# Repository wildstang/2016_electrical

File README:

This is the 2015 electrical repository.

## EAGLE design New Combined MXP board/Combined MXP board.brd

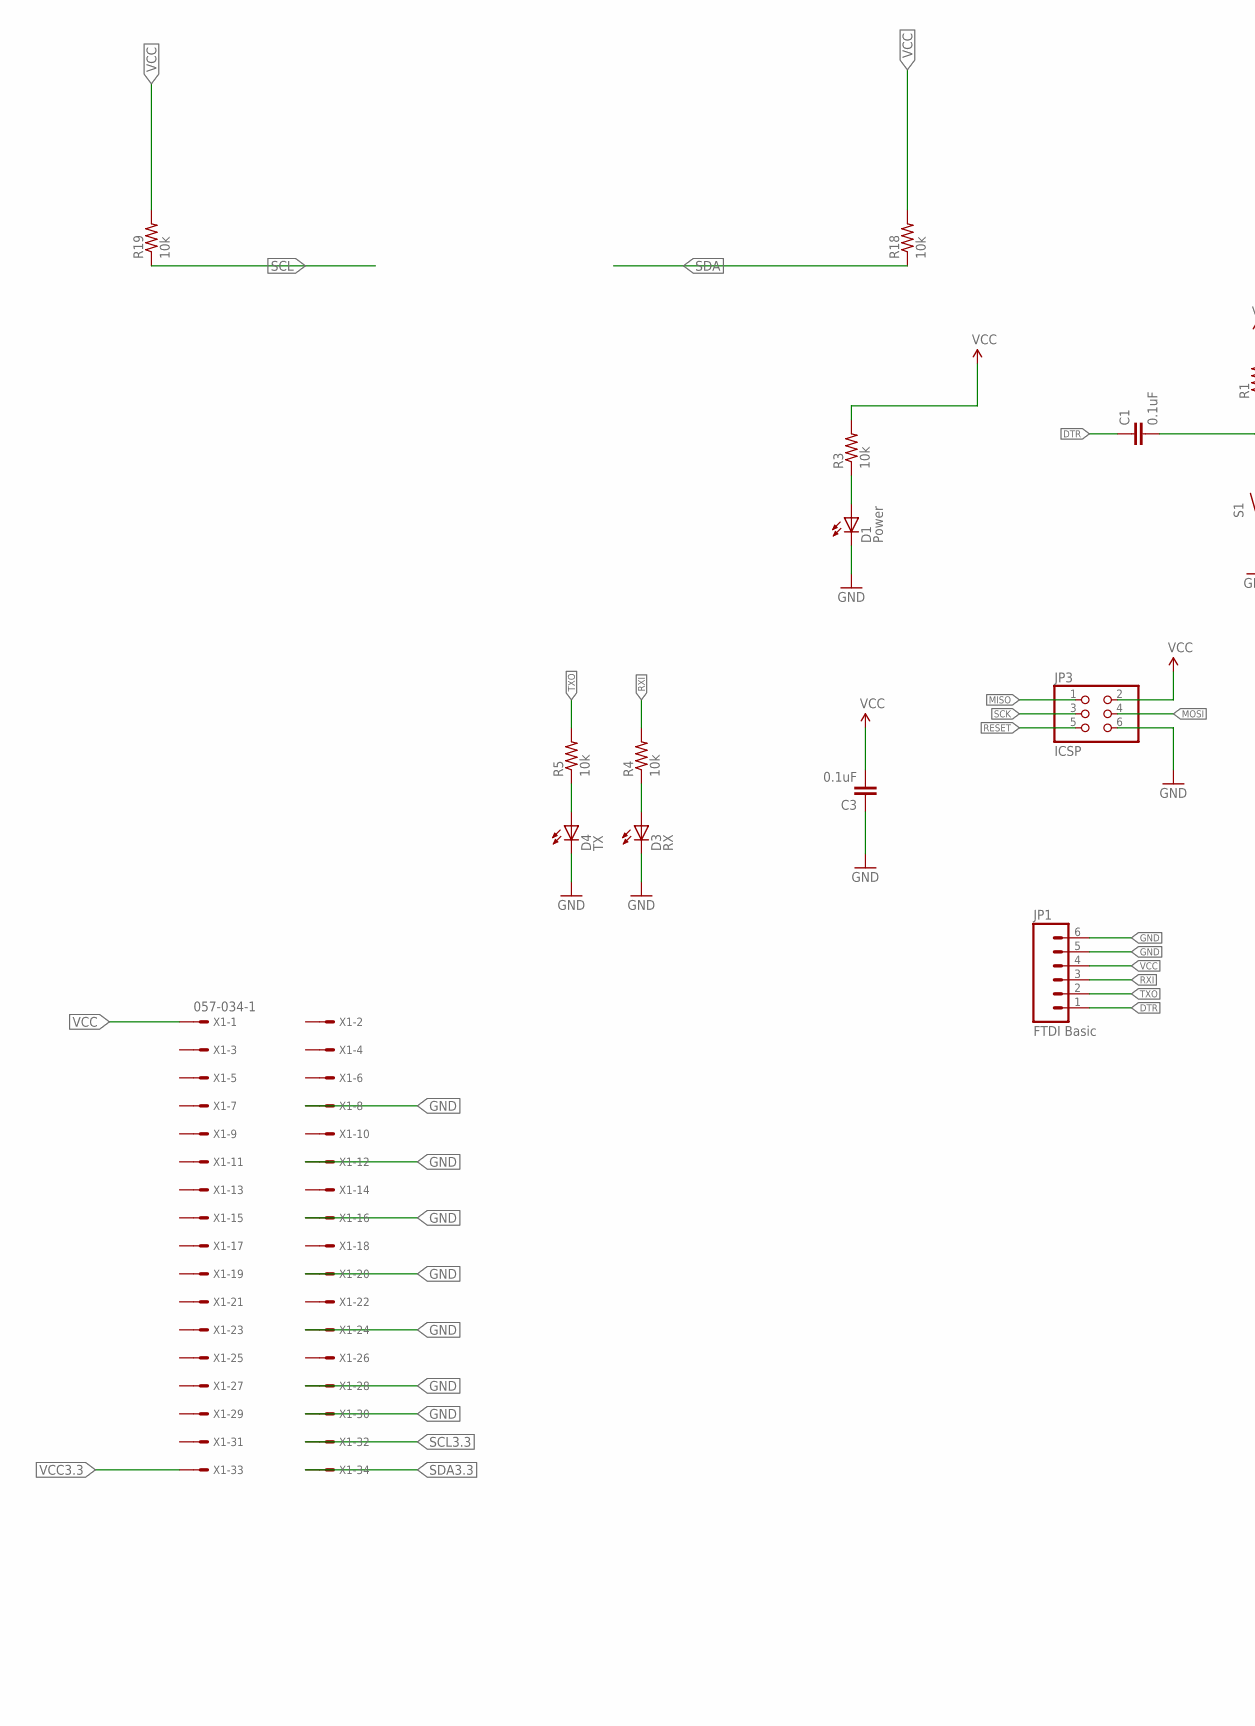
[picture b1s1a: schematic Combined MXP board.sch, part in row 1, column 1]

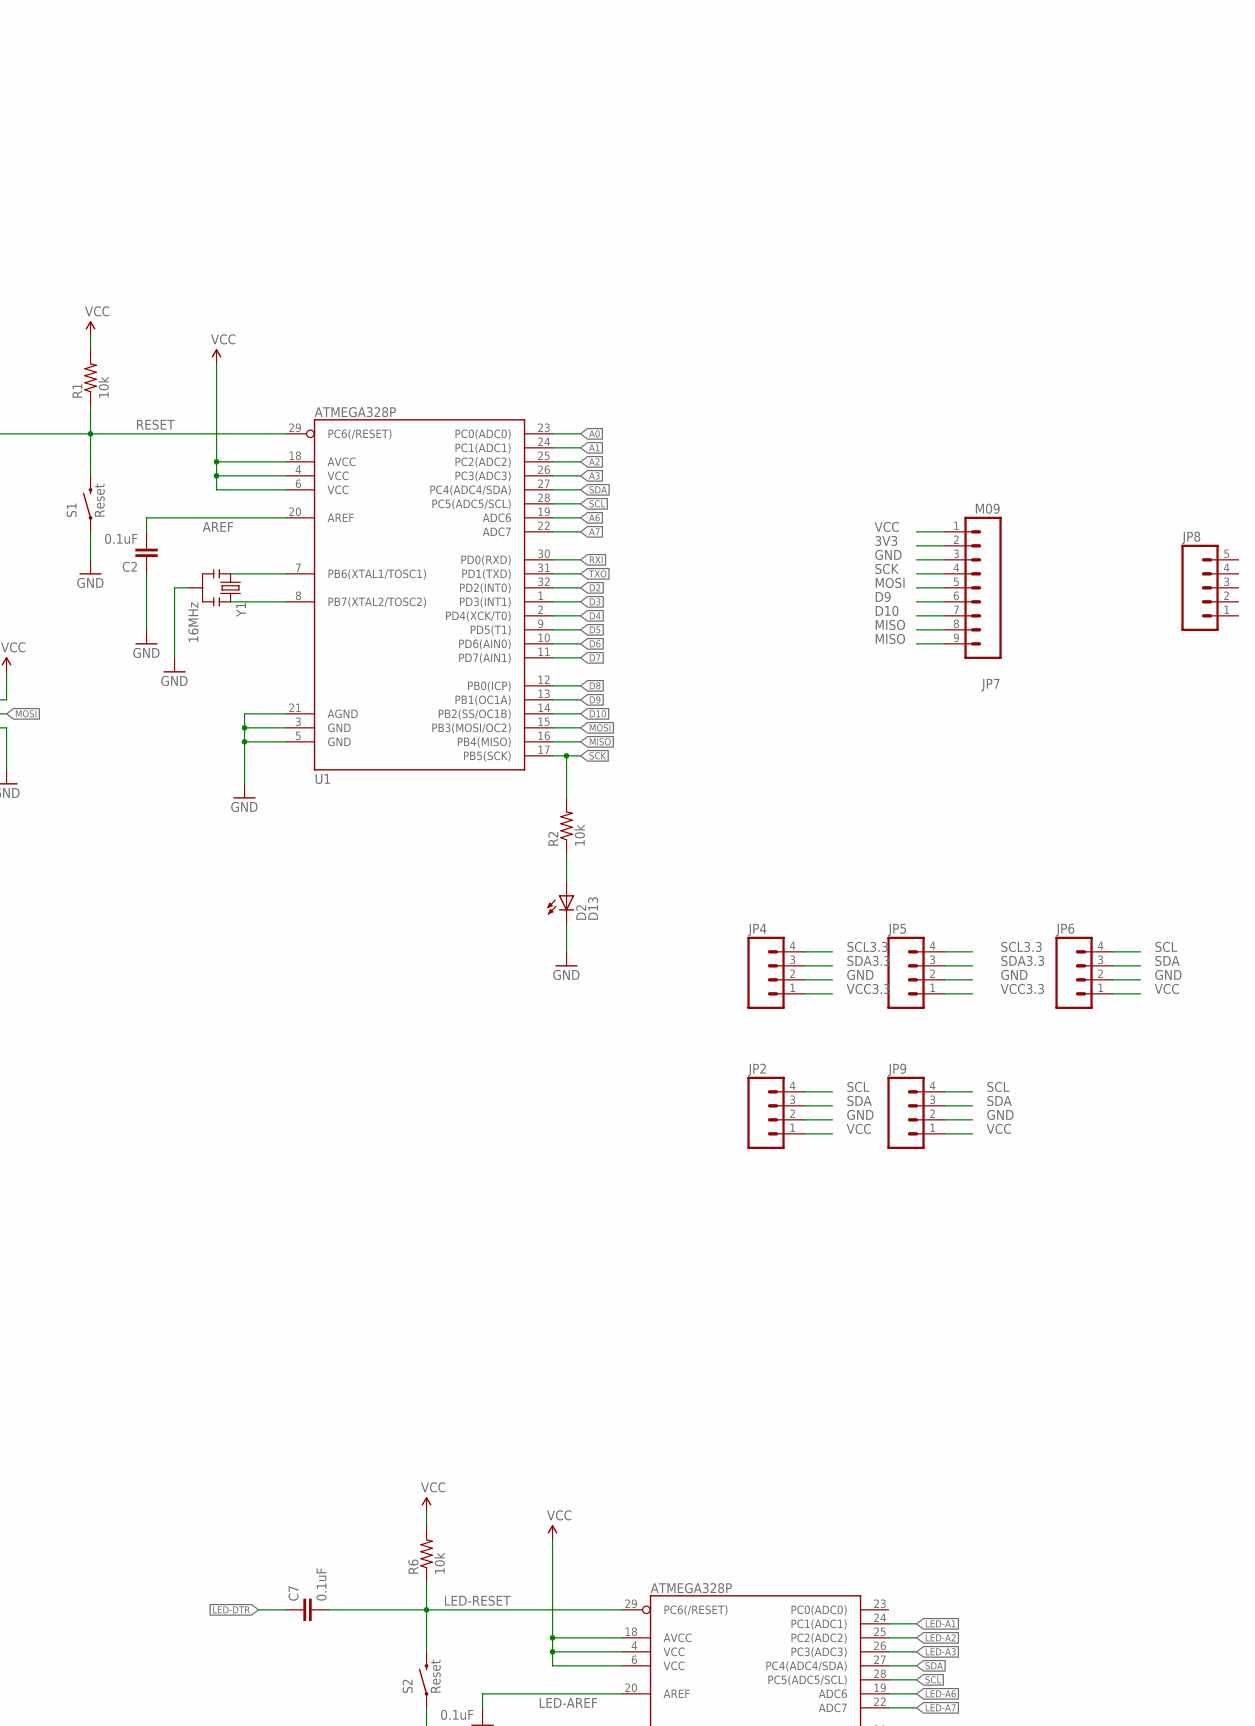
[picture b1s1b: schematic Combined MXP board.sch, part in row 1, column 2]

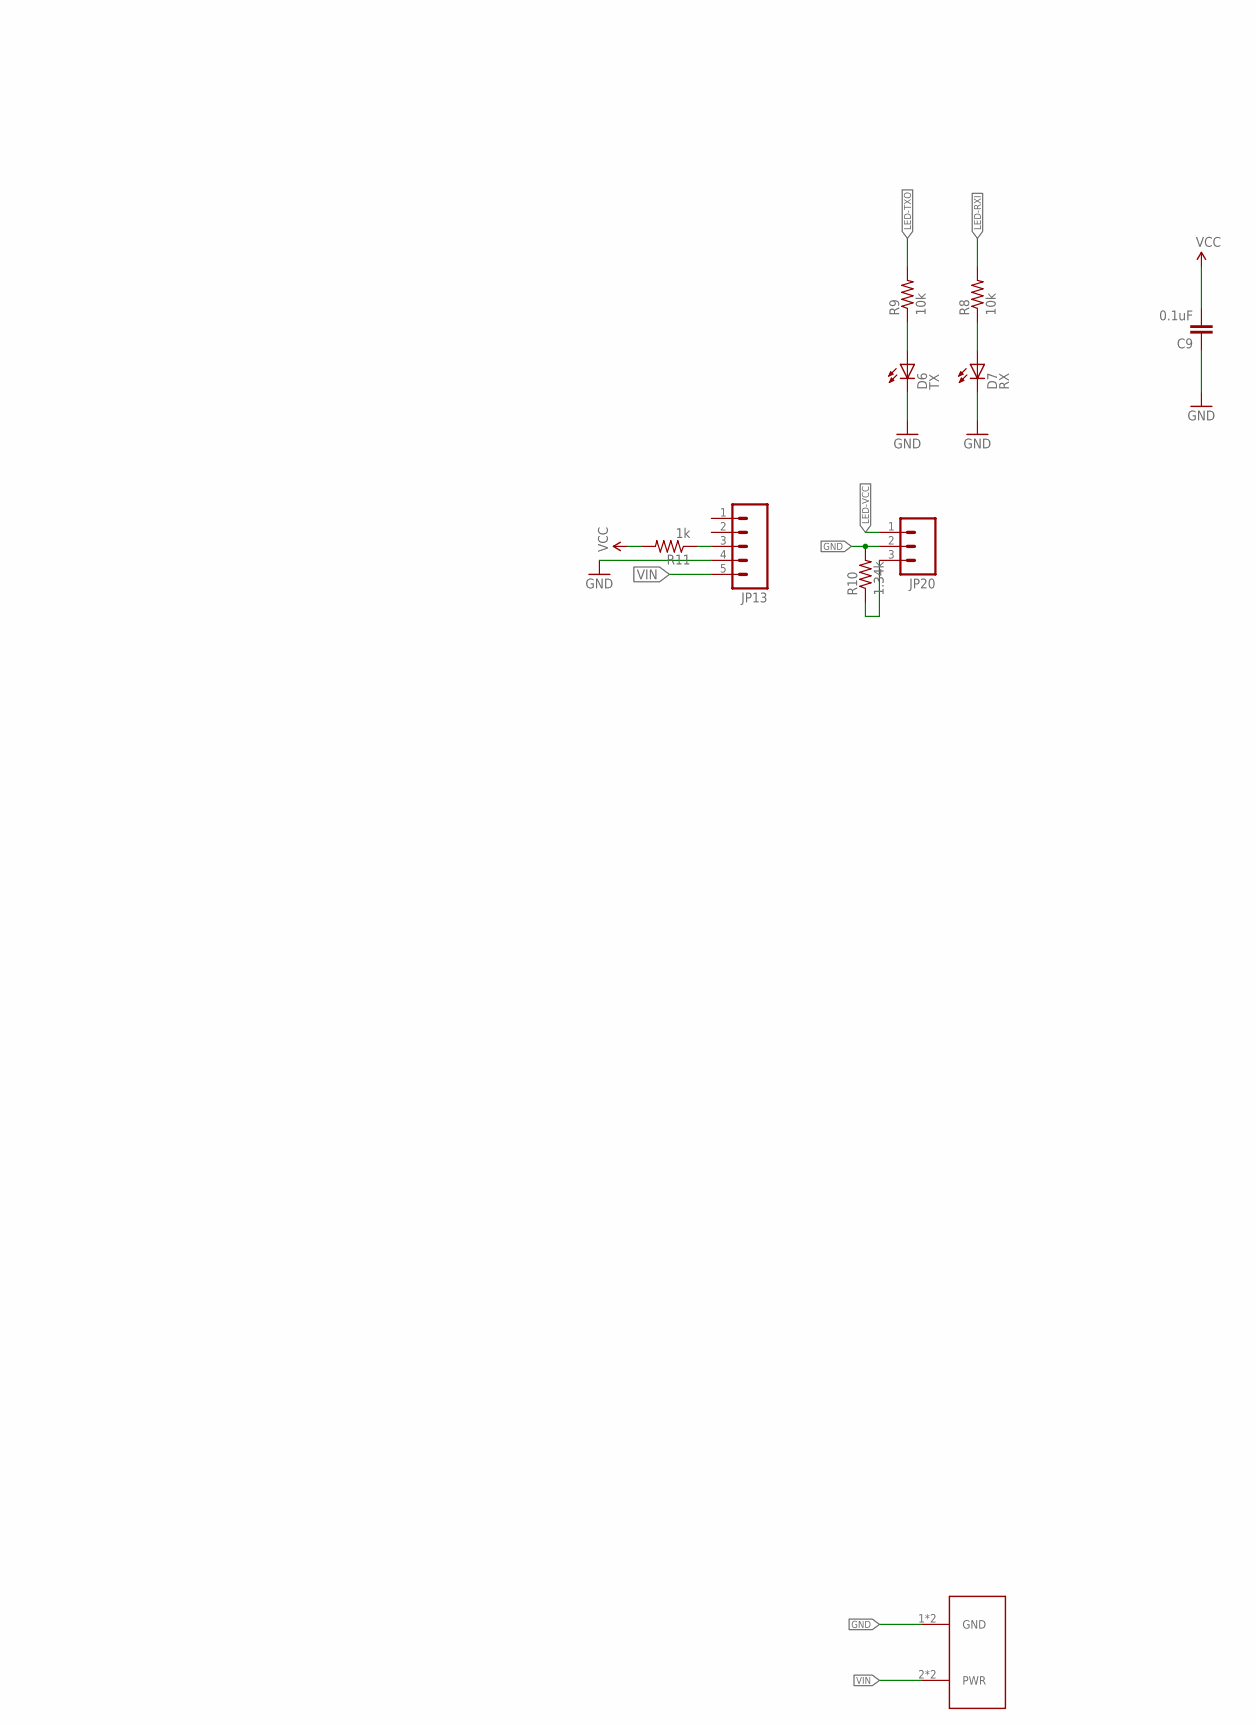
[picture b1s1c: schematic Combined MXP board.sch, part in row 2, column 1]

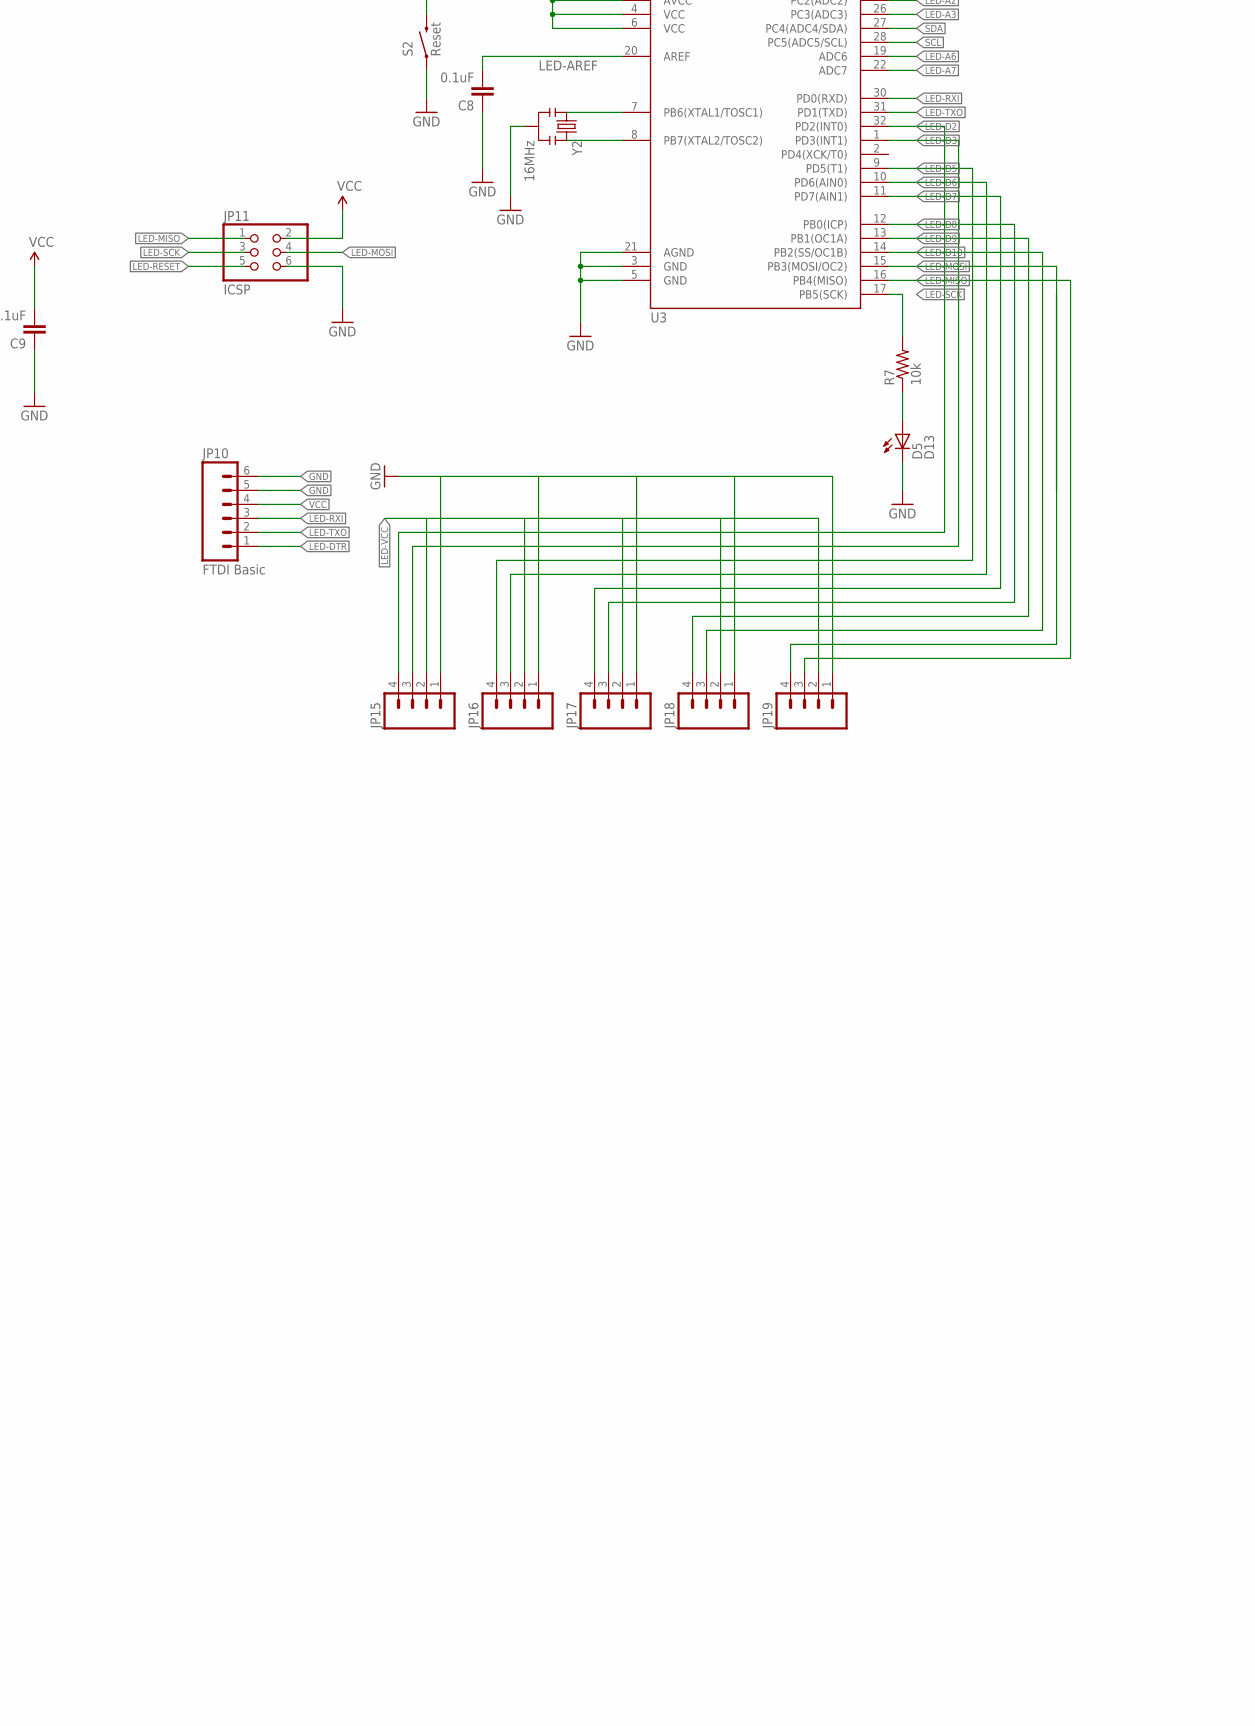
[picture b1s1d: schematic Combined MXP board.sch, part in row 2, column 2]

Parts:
C1, C2, C3, C7, C8, C9: 0.1uF; 0603-CAP
D1: Power; LED-0603
D2, D5: D13; LED-0603
D3, D7: RX; LED-0603
D4, D6: TX; LED-0603
JP1, JP10: FTDI Basic; 1X06
JP2, JP4, JP5, JP6, JP9, JP15, JP16, JP17, JP18, JP19: M04PTH; 1X04
JP3, JP11: ICSP; 2X03
JP7: M09; 1X09
JP8, JP13: M05PTH; 1X05
JP20: M03PTH; 1X03
R1, R2, R3, R4, R5, R6, R7, R8, R9, R18, R19: 10k; 0603-RES
R10: 1.34k; AXIAL-0.3
R11: 1k; AXIAL-0.3
S1, S2: Reset; TACTILE_SWITCH_SMD
U1, U3: ATMEGA328P; TQFP32-08
U$2: LSF-SMT
X1: 057-034-1
Y1, Y2: 16MHz; RESONATOR-SMD

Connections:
3V3: JP7.2
A0: U1.23 (PC0(ADC0))
A1: U1.24 (PC1(ADC1))
A2: U1.25 (PC2(ADC2))
A3: U1.26 (PC3(ADC3))
A6: U1.19 (ADC6)
A7: U1.22 (ADC7)
AREF: C2.2, U1.20 (AREF)
D2: U1.32 (PD2(INT0))
D3: U1.1 (PD3(INT1))
D4: U1.2 (PD4(XCK/T0))
D5: U1.9 (PD5(T1))
D6: U1.10 (PD6(AIN0))
D7: U1.11 (PD7(AIN1))
D8: U1.12 (PB0(ICP))
D9: JP7.6, U1.13 (PB1(OC1A))
D10: JP7.7, U1.14 (PB2(SS/OC1B))
DTR: C1.1, JP1.1
GND: C2.1, C3.1, C8.1, C9.1, D1.C, D2.C, D3.C, D4.C, D5.C, D6.C, D7.C, JP1.5, JP1.6, JP2.2, JP3.6, JP4.2, JP5.2, JP6.2, JP7.3, JP9.2, JP10.5, JP10.6, JP11.6, JP13.4, JP15.1, JP16.1, JP17.1, JP18.1, JP19.1, JP20.2, R10.P$2 (2), S1.1, S2.1, U1.3 (GND), U1.5 (GND), U1.21 (AGND), U3.3 (GND), U3.5 (GND), U3.21 (AGND), U$2.1 (GND), U$2.1-2 (GND), X1.8, X1.12, X1.16, X1.20, X1.24, X1.28, X1.30, Y1.2, Y2.2
LED-A1: U3.24 (PC1(ADC1))
LED-A2: U3.25 (PC2(ADC2))
LED-A3: U3.26 (PC3(ADC3))
LED-A6: U3.19 (ADC6)
LED-A7: U3.22 (ADC7)
LED-AREF: C8.2, U3.20 (AREF)
LED-D2: JP15.4, U3.32 (PD2(INT0))
LED-D3: JP15.3, U3.1 (PD3(INT1))
LED-D5: JP16.4, U3.9 (PD5(T1))
LED-D6: JP16.3, U3.10 (PD6(AIN0))
LED-D7: JP17.4, U3.11 (PD7(AIN1))
LED-D8: JP17.3, U3.12 (PB0(ICP))
LED-D9: JP18.4, U3.13 (PB1(OC1A))
LED-D10: JP18.3, U3.14 (PB2(SS/OC1B))
LED-DTR: C7.1, JP10.1
LED-MISO: JP11.1, JP19.3, U3.16 (PB4(MISO))
LED-MOSI: JP11.4, JP19.4, U3.15 (PB3(MOSI/OC2))
LED-RESET: C7.2, JP11.5, R6.1, S2.3 (2), U3.29 (PC6(/RESET))
LED-RXI: JP10.3, R8.2, U3.30 (PD0(RXD))
LED-SCK: JP11.3, R7.2, U3.17 (PB5(SCK))
LED-TXO: JP10.2, R9.2, U3.31 (PD1(TXD))
LED-VCC: JP15.2, JP16.2, JP17.2, JP18.2, JP19.2, JP20.1
MISO: JP3.1, JP7.8, JP7.9, U1.16 (PB4(MISO))
MOSI: JP3.4, JP7.5, U1.15 (PB3(MOSI/OC2))
unnamed: U1.7 (PB6(XTAL1/TOSC1)), Y1.1
unnamed: U1.8 (PB7(XTAL2/TOSC2)), Y1.3
unnamed: D1.A, R3.1
unnamed: D2.A, R2.1
unnamed: D3.A, R4.1
unnamed: D4.A, R5.1
unnamed: U3.7 (PB6(XTAL1/TOSC1)), Y2.1
unnamed: U3.8 (PB7(XTAL2/TOSC2)), Y2.3
unnamed: D5.A, R7.1
unnamed: D6.A, R9.1
unnamed: D7.A, R8.1
unnamed: JP20.3, R10.P$1 (1)
unnamed: JP13.3, R11.P$1 (1)
RESET: C1.2, JP3.5, R1.1, S1.3 (2), U1.29 (PC6(/RESET))
RXI: JP1.3, R4.2, U1.30 (PD0(RXD))
SCK: JP3.3, JP7.4, R2.2, U1.17 (PB5(SCK))
SCL: JP2.4, JP6.4, JP9.4, R19.1, U1.28 (PC5(ADC5/SCL)), U3.28 (PC5(ADC5/SCL))
SCL3.3: JP4.4, JP5.4, X1.32
SDA: JP2.3, JP6.3, JP9.3, R18.1, U1.27 (PC4(ADC4/SDA)), U3.27 (PC4(ADC4/SDA))
SDA3.3: JP4.3, JP5.3, X1.34
TXO: JP1.2, R5.2, U1.31 (PD1(TXD))
VCC: C3.2, C9.2, JP1.4, JP2.1, JP3.2, JP6.1, JP7.1, JP9.1, JP10.4, JP11.2, R1.2, R3.2, R6.2, R11.P$2 (2), R18.2, R19.2, U1.4 (VCC), U1.6 (VCC), U1.18 (AVCC), U3.4 (VCC), U3.6 (VCC), U3.18 (AVCC), X1.1
VCC3.3: JP4.1, JP5.1, X1.33
VIN: JP13.5, U$2.2 (PWR), U$2.2-2 (PWR)

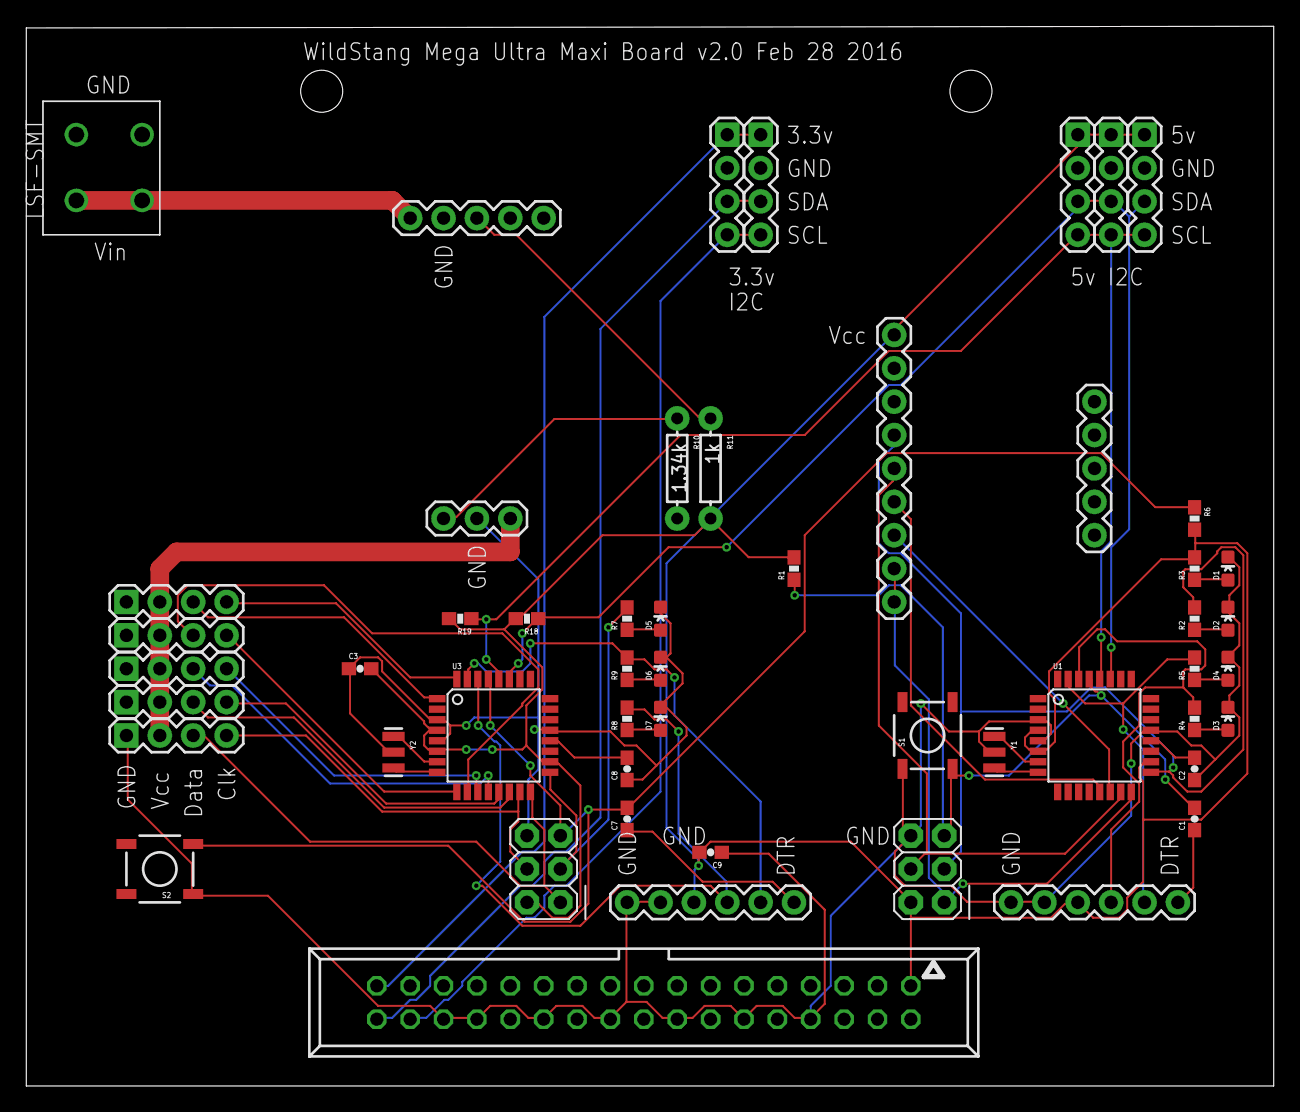
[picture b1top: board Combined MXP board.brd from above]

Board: 2 copper layers, 94.9 x 80.6 mm, 52 parts (0 on the bottom side), 48 nets.

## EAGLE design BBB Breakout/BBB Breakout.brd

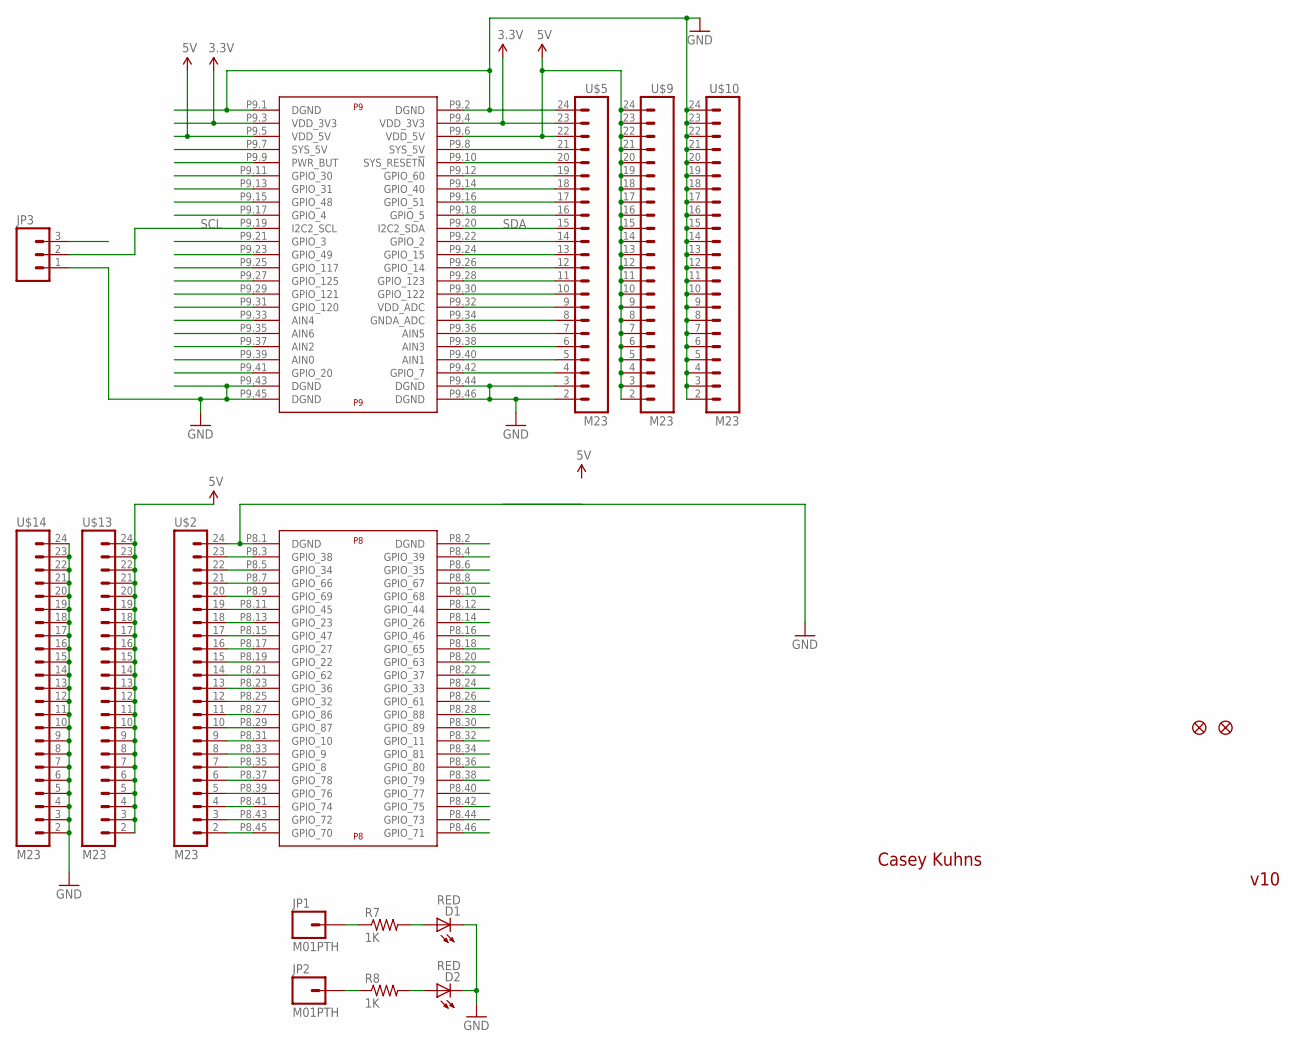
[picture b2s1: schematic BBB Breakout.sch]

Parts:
D1, D2: RED; LED-0603
FID1, FID2: FIDUCIAL1X2; FIDUCIAL-1X2
JP1, JP2: M01PTH; 1X01
JP3: M03PTH; 1X03
R7, R8: 1K; 0603-RES
U$1: BEAGLE_BONE_BLACK_CAPE
U$2, U$5, U$9, U$10, U$13, U$14: M23; 1X23

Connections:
3.3V: U$1.P9.3 (VDD_3V3), U$1.P9.4 (VDD_3V3), U$5.23
5V: U$1.P9.5 (VDD_5V), U$1.P9.6 (VDD_5V), U$5.22, U$9.2, U$9.3, U$9.4, U$9.5, U$9.6, U$9.7, U$9.8, U$9.9, U$9.10, U$9.11, U$9.12, U$9.13, U$9.14, U$9.15, U$9.16, U$9.17, U$9.18, U$9.19, U$9.20, U$9.21, U$9.22, U$9.23, U$9.24, U$13.2, U$13.3, U$13.4, U$13.5, U$13.6, U$13.7, U$13.8, U$13.9, U$13.10, U$13.11, U$13.12, U$13.13, U$13.14, U$13.15, U$13.16, U$13.17, U$13.18, U$13.19, U$13.20, U$13.21, U$13.22, U$13.23, U$13.24
GND: D1.C, D2.C, JP3.1, U$1.P8.1 (DGND), U$1.P9.1 (DGND), U$1.P9.2 (DGND), U$1.P9.43 (DGND), U$1.P9.44 (DGND), U$1.P9.45 (DGND), U$1.P9.46 (DGND), U$2.24, U$5.2, U$5.3, U$5.24, U$10.2, U$10.3, U$10.4, U$10.5, U$10.6, U$10.7, U$10.8, U$10.9, U$10.10, U$10.11, U$10.12, U$10.13, U$10.14, U$10.15, U$10.16, U$10.17, U$10.18, U$10.19, U$10.20, U$10.21, U$10.22, U$10.23, U$10.24, U$14.2, U$14.3, U$14.4, U$14.5, U$14.6, U$14.7, U$14.8, U$14.9, U$14.10, U$14.11, U$14.12, U$14.13, U$14.14, U$14.15, U$14.16, U$14.17, U$14.18, U$14.19, U$14.20, U$14.21, U$14.22, U$14.23, U$14.24
unnamed: U$1.P8.45 (GPIO_70), U$2.2
unnamed: D1.A, R7.2
unnamed: U$1.P8.43 (GPIO_72), U$2.3
unnamed: U$1.P8.41 (GPIO_74), U$2.4
unnamed: D2.A, R8.2
unnamed: JP1.1, R7.1
unnamed: U$1.P8.39 (GPIO_76), U$2.5
unnamed: U$1.P8.37 (GPIO_78), U$2.6
unnamed: U$1.P8.35 (GPIO_8), U$2.7
unnamed: U$1.P8.33 (GPIO_9), U$2.8
unnamed: U$1.P8.31 (GPIO_10), U$2.9
unnamed: U$1.P8.29 (GPIO_87), U$2.10
unnamed: U$1.P8.27 (GPIO_86), U$2.11
unnamed: U$1.P8.25 (GPIO_32), U$2.12
unnamed: U$1.P8.23 (GPIO_36), U$2.13
unnamed: U$1.P8.21 (GPIO_62), U$2.14
unnamed: U$1.P8.19 (GPIO_22), U$2.15
unnamed: U$1.P8.17 (GPIO_27), U$2.16
unnamed: U$1.P8.15 (GPIO_47), U$2.17
unnamed: U$1.P8.13 (GPIO_23), U$2.18
unnamed: U$1.P8.11 (GPIO_45), U$2.19
unnamed: U$1.P8.9 (GPIO_69), U$2.20
unnamed: U$1.P8.7 (GPIO_66), U$2.21
unnamed: U$1.P8.5 (GPIO_34), U$2.22
unnamed: U$1.P8.3 (GPIO_38), U$2.23
unnamed: JP2.1, R8.1
unnamed: U$1.P9.42 (GPIO_7), U$5.4
unnamed: U$1.P9.40 (AIN1), U$5.5
unnamed: U$1.P9.38 (AIN3), U$5.6
unnamed: U$1.P9.36 (AIN5), U$5.7
unnamed: U$1.P9.34 (GNDA_ADC), U$5.8
unnamed: U$1.P9.32 (VDD_ADC), U$5.9
unnamed: U$1.P9.30 (GPIO_122), U$5.10
unnamed: U$1.P9.28 (GPIO_123), U$5.11
unnamed: U$1.P9.26 (GPIO_14), U$5.12
unnamed: U$1.P9.24 (GPIO_15), U$5.13
unnamed: U$1.P9.22 (GPIO_2), U$5.14
unnamed: U$1.P9.18 (GPIO_5), U$5.16
unnamed: U$1.P9.16 (GPIO_51), U$5.17
unnamed: U$1.P9.14 (GPIO_40), U$5.18
unnamed: U$1.P9.12 (GPIO_60), U$5.19
unnamed: U$1.P9.10 (SYS_RESET!N), U$5.20
unnamed: U$1.P9.8 (SYS_5V), U$5.21
SCL: JP3.2, U$1.P9.19 (I2C2_SCL)
SDA: JP3.3, U$1.P9.20 (I2C2_SDA), U$5.15

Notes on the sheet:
Casey Kuhns
v10

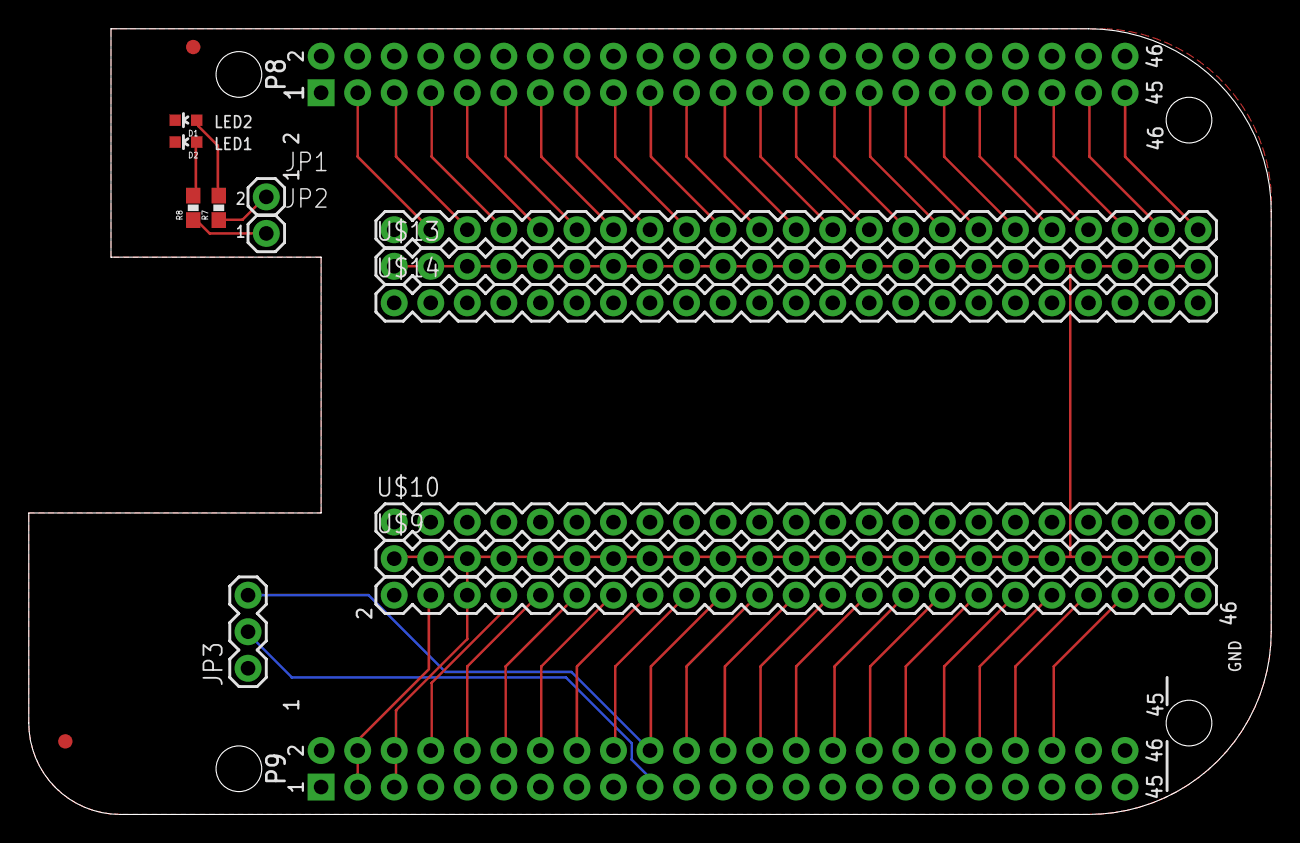
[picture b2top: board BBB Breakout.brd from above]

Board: 2 copper layers, 86.4 x 54.6 mm, 16 parts (0 on the bottom side), 48 nets.

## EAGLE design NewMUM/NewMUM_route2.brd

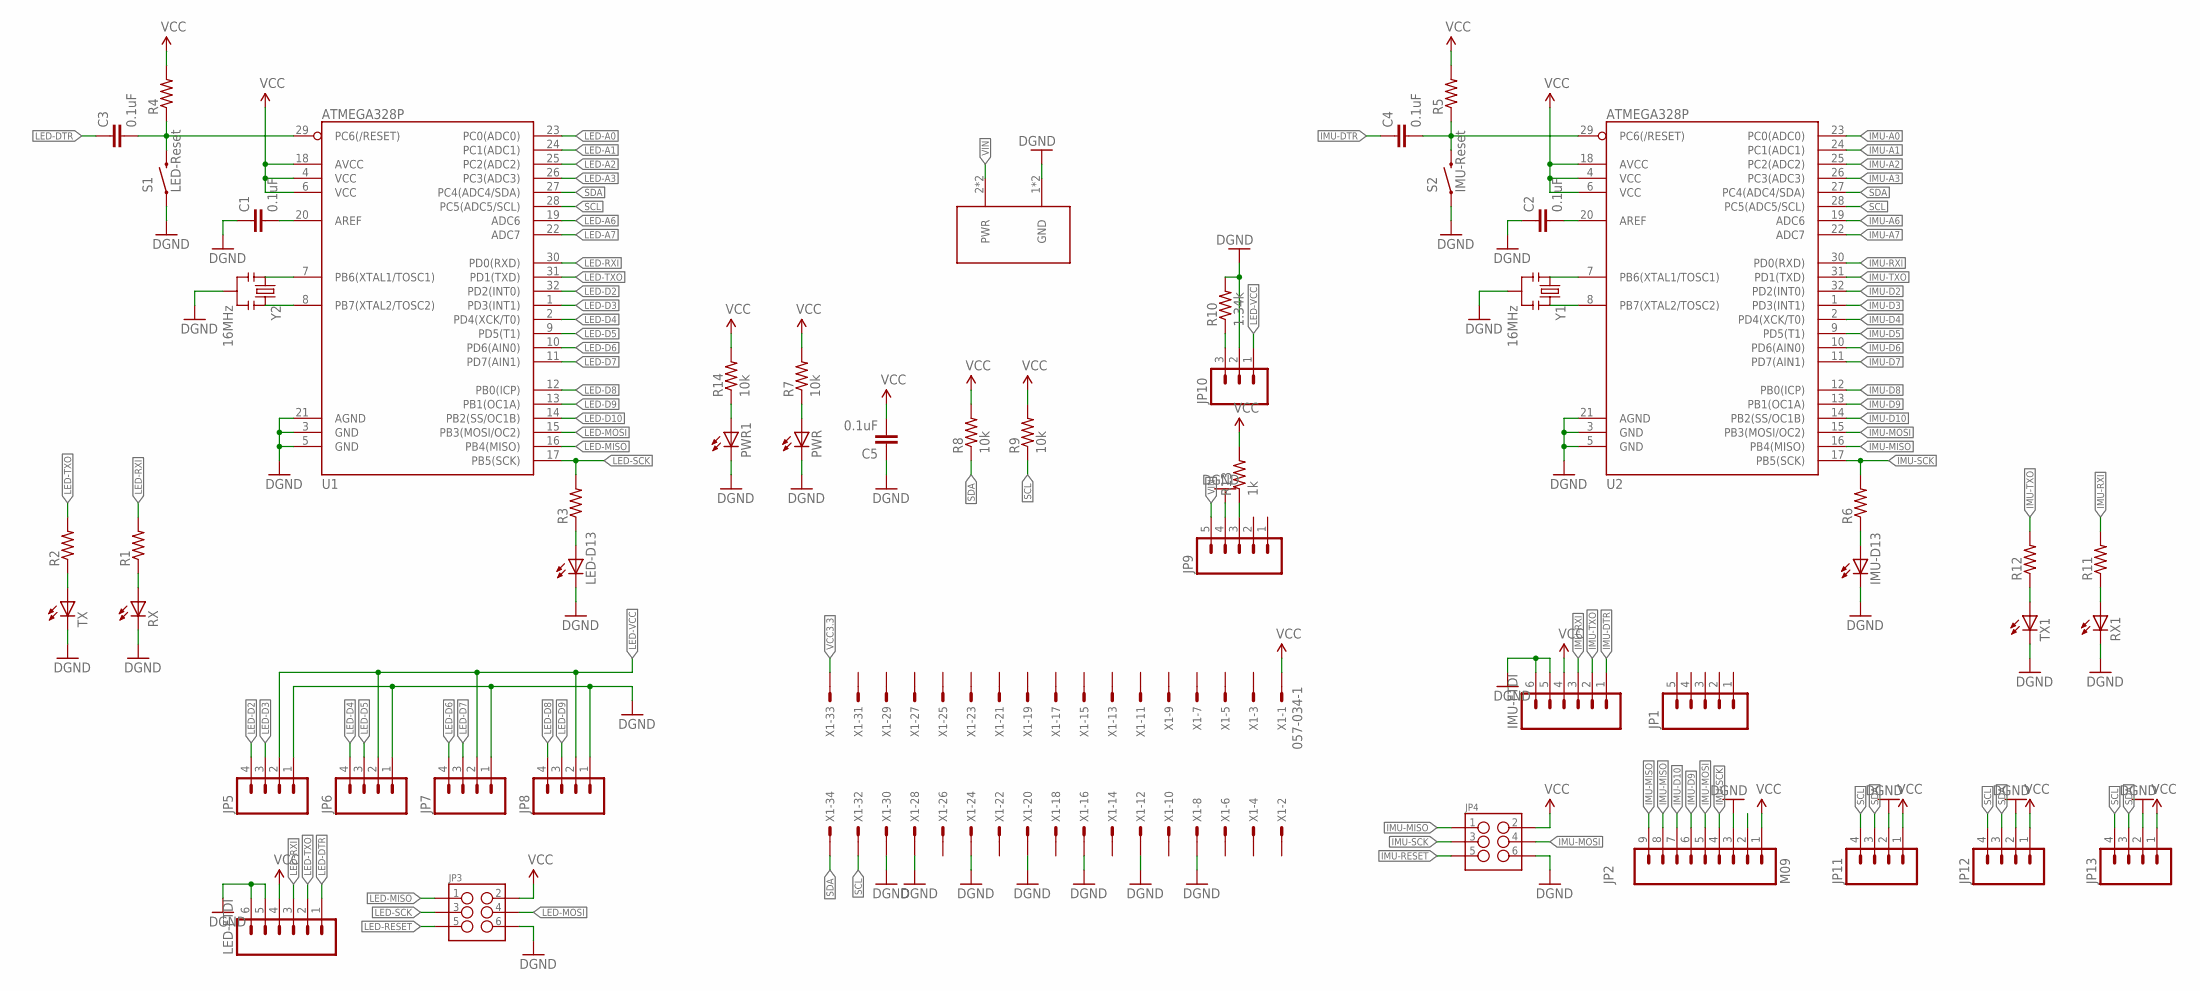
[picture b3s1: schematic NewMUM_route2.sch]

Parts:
C1, C2, C3, C4, C5: 0.1uF; 0805
IMU-D13: LED1206; LED-1206
IMU-FTDI: M06SIP; 1X06
JP1, JP9: M05PTH; 1X05
JP2: M09; 1X09
JP3, JP4: M03X22X3_SILK_SM; 2X3
JP5, JP6, JP7, JP8, JP11, JP12, JP13: M04PTH; 1X04
JP10: M03PTH; 1X03
LED-D13: LED1206; LED-1206
LED-FTDI: M06SIP; 1X06
PWR, PWR1: LED1206; LED-1206
R1, R2, R3, R4, R5, R6, R11, R12: RESISTOR0805-RES; 0805
R7, R8, R9, R14: 10k; 0805
R10: 1.34k; AXIAL-0.3EZ
R13: 1k; 0805
RX, RX1: LED1206; LED-1206
S1: LED-Reset; TACTILE-PTH
S2: IMU-Reset; TACTILE-PTH
TX, TX1: LED1206; LED-1206
U1, U2: ATMEGA328P; TQFP32-08
U$3: LSF-SMT
X1: 057-034-1
Y1, Y2: 16MHz; RESONATOR-SMD

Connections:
GND: C1.1, C2.1, C5.1, IMU-D13.C, IMU-FTDI.5, IMU-FTDI.6, JP2.3, JP3.6, JP4.6, JP5.1, JP6.1, JP7.1, JP8.1, JP9.4, JP10.2, JP11.2, JP12.2, JP13.2, LED-D13.C, LED-FTDI.5, LED-FTDI.6, PWR.C, PWR1.C, R10.P$2 (2), RX.C, RX1.C, S1.1, S2.1, TX.C, TX1.C, U1.3 (GND), U1.5 (GND), U1.21 (AGND), U2.3 (GND), U2.5 (GND), U2.21 (AGND), U$3.1 (GND), U$3.1-2 (GND), X1.8, X1.12, X1.16, X1.20, X1.24, X1.28, X1.30, Y1.2, Y2.2
IMU-A0: U2.23 (PC0(ADC0))
IMU-A1: U2.24 (PC1(ADC1))
IMU-A2: U2.25 (PC2(ADC2))
IMU-A3: U2.26 (PC3(ADC3))
IMU-A6: U2.19 (ADC6)
IMU-A7: U2.22 (ADC7)
IMU-D2: U2.32 (PD2(INT0))
IMU-D3: U2.1 (PD3(INT1))
IMU-D4: U2.2 (PD4(XCK/T0))
IMU-D5: U2.9 (PD5(T1))
IMU-D6: U2.10 (PD6(AIN0))
IMU-D7: U2.11 (PD7(AIN1))
IMU-D8: U2.12 (PB0(ICP))
IMU-D9: JP2.6, U2.13 (PB1(OC1A))
IMU-D10: JP2.7, U2.14 (PB2(SS/OC1B))
IMU-DTR: C4.1, IMU-FTDI.1
IMU-MISO: JP2.8, JP2.9, JP4.1, U2.16 (PB4(MISO))
IMU-MOSI: JP2.5, JP4.4, U2.15 (PB3(MOSI/OC2))
IMU-RESET: C4.2, JP4.5, R5.1, S2.3 (2), U2.29 (PC6(/RESET))
IMU-RXI: IMU-FTDI.3, R11.2, U2.30 (PD0(RXD))
IMU-SCK: JP2.4, JP4.3, R6.2, U2.17 (PB5(SCK))
IMU-TXO: IMU-FTDI.2, R12.2, U2.31 (PD1(TXD))
LED-A0: U1.23 (PC0(ADC0))
LED-A1: U1.24 (PC1(ADC1))
LED-A2: U1.25 (PC2(ADC2))
LED-A3: U1.26 (PC3(ADC3))
LED-A6: U1.19 (ADC6)
LED-A7: U1.22 (ADC7)
LED-D2: JP5.4, U1.32 (PD2(INT0))
LED-D3: JP5.3, U1.1 (PD3(INT1))
LED-D4: JP6.4, U1.2 (PD4(XCK/T0))
LED-D5: JP6.3, U1.9 (PD5(T1))
LED-D6: JP7.4, U1.10 (PD6(AIN0))
LED-D7: JP7.3, U1.11 (PD7(AIN1))
LED-D8: JP8.4, U1.12 (PB0(ICP))
LED-D9: JP8.3, U1.13 (PB1(OC1A))
LED-D10: U1.14 (PB2(SS/OC1B))
LED-DTR: C3.1, LED-FTDI.1
LED-MISO: JP3.1, U1.16 (PB4(MISO))
LED-MOSI: JP3.4, U1.15 (PB3(MOSI/OC2))
LED-RESET: C3.2, JP3.5, R4.1, S1.3 (2), U1.29 (PC6(/RESET))
LED-RXI: LED-FTDI.3, R1.2, U1.30 (PD0(RXD))
LED-SCK: JP3.3, R3.2, U1.17 (PB5(SCK))
LED-TXO: LED-FTDI.2, R2.2, U1.31 (PD1(TXD))
LED-VCC: JP5.2, JP6.2, JP7.2, JP8.2, JP10.1
unnamed: U2.8 (PB7(XTAL2/TOSC2)), Y1.3
unnamed: U2.7 (PB6(XTAL1/TOSC1)), Y1.1
unnamed: U1.8 (PB7(XTAL2/TOSC2)), Y2.3
unnamed: U1.7 (PB6(XTAL1/TOSC1)), Y2.1
unnamed: R1.1, RX.A
unnamed: C1.2, U1.20 (AREF)
unnamed: C2.2, U2.20 (AREF)
unnamed: R2.1, TX.A
unnamed: LED-D13.A, R3.1
unnamed: R11.1, RX1.A
unnamed: IMU-D13.A, R6.1
unnamed: R12.1, TX1.A
unnamed: PWR.A, R7.1
unnamed: JP9.3, R13.1
unnamed: PWR1.A, R14.1
unnamed: JP10.3, R10.P$1 (1)
SCL: JP11.4, JP12.4, JP13.4, R9.1, U1.28 (PC5(ADC5/SCL)), U2.28 (PC5(ADC5/SCL)), X1.32
SDA: JP11.3, JP12.3, JP13.3, R8.1, U1.27 (PC4(ADC4/SDA)), U2.27 (PC4(ADC4/SDA)), X1.34
VCC: C5.2, IMU-FTDI.4, JP2.1, JP3.2, JP4.2, JP11.1, JP12.1, JP13.1, LED-FTDI.4, R4.2, R5.2, R7.2, R8.2, R9.2, R13.2, R14.2, U1.4 (VCC), U1.6 (VCC), U1.18 (AVCC), U2.4 (VCC), U2.6 (VCC), U2.18 (AVCC), X1.1
VCC3.3: X1.33
VIN: JP9.5, U$3.2 (PWR), U$3.2-2 (PWR)

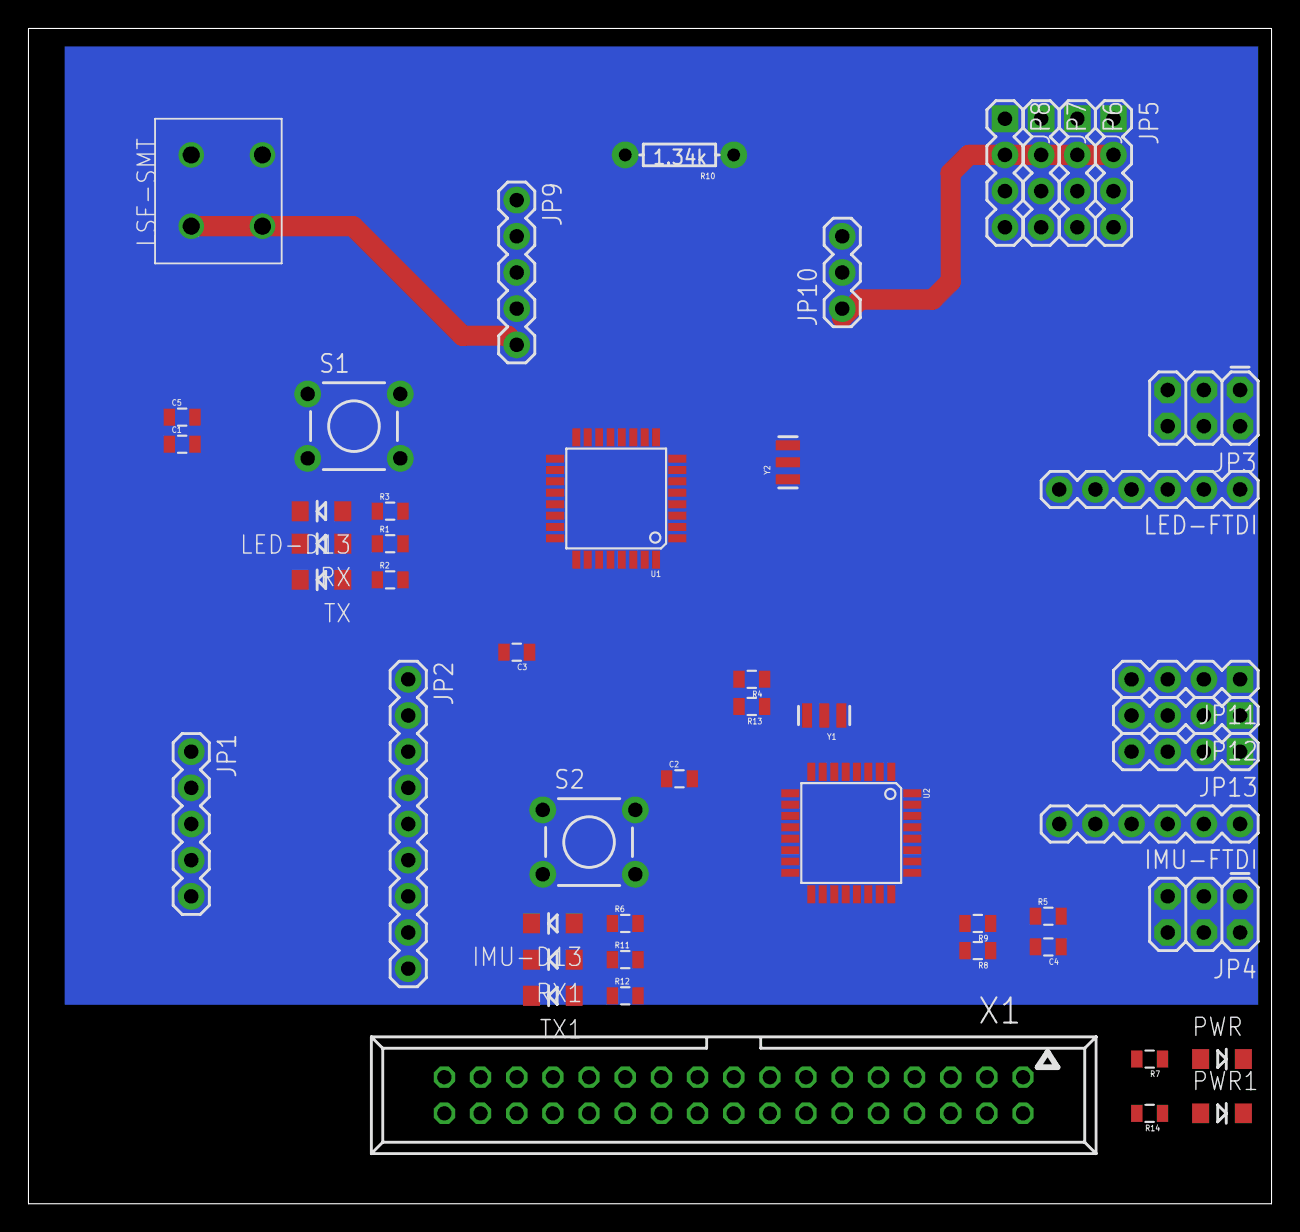
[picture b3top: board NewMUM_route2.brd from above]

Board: 2 copper layers, 87.3 x 82.5 mm, 50 parts (0 on the bottom side), 46 nets.

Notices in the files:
parts and their libraries:
SparkFun-Boards: Licensing: CC v3.0 Share-Alike You are welcome to use this library for commercial purposes.
SparkFun-LED: Licensing: Creative Commons ShareAlike 4.0 International - https://creativecommons.org/licenses/by-sa/4.0
